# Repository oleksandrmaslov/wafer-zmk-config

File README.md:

# Wafer

Wafer is a 36 key ultra-thin split keyboard that stays between 4–8 mm thick,
depending where you measure it. It runs on an ISP1807 with an nPM1300 PMIC, and
the full aluminium case snaps together with magnets for a clean profile.
Kailh PG1316S switches, a nice!view display and a 250 mAh LiPo in each half.
It runs ZMK over Bluetooth LE or USB.

More photos and the full story are on
[the project page](https://oleksandrmaslov.github.io/portfolio/Wafer.html).

***

## LAYOUT

Default layout is shown above; layers and firmware live in this repo. `main`
keeps the standard QWERTY layout, and my daily-use keymap is on
[`personal-layout`](https://github.com/oleksandrmaslov/wafer-zmk-config/tree/personal-layout).
Copy [wafer.keymap](boards/waferboard/wafer/wafer.keymap) to `config/wafer.keymap`
to change it, and put your other settings in [config/wafer.conf](config/wafer.conf).

The default build keeps the local nice!view status screen and
[zmk-soft-off-plus](https://github.com/oleksandrmaslov/zmk-soft-off-plus).
Hold the power button for about 1.8 seconds, then release it to turn both
connected halves off. On battery, hold each half's button for 1.5 seconds to
wake it. USB wake bypass allows a short press when USB power is detected.
Triple-tap the plugged-in half's button while awake to enter its bootloader.

The [nPM1300 battery driver](modules/npm1300_vbat/) lives here. Soft-off-plus and
[zmk-split-hid-display](https://github.com/oleksandrmaslov/zmk-split-hid-display)
stay in their own separate repos. The HID display module is optional and adds
the host information shown in the newer display photos. Check **hid_display** in a manual
[build workflow](https://github.com/oleksandrmaslov/wafer-zmk-config/actions/workflows/build.yml)
run to build that version too.

[Build and flashing guide](docs/building.md) ·
[Board files](boards/waferboard/wafer/README.md) ·
[Build validation](docs/validation.md)

***

## PCB

[Here](https://github.com/oleksandrmaslov/wafer-keyboard/tree/main/pcb) you can
find the PCB and production files in the separate `wafer-keyboard` repo. There
are two versions, with mousebites for production and without them.

***

## BOM

The full Bill of Materials is in the hardware repo:

- [BOM (JLCPCB production)](https://github.com/oleksandrmaslov/wafer-keyboard/blob/main/pcb/jlcpcb/production_files/BOM-wafer_keyboard_v3_production.csv)
- [Component placement](https://github.com/oleksandrmaslov/wafer-keyboard/blob/main/pcb/jlcpcb/production_files/CPL-wafer_keyboard_v3_production.csv)
- [Original price breakdown](https://github.com/oleksandrmaslov/wafer-keyboard/blob/main/pcb/Keyboard%20Price.csv)

***

## CASE

These models are for CNC:

- [Left case STEP](https://github.com/oleksandrmaslov/wafer-keyboard/blob/main/case/wafer_case_left.step)
- [Right case STEP](https://github.com/oleksandrmaslov/wafer-keyboard/blob/main/case/wafer_case_right.step)
- [Thread drawing](https://github.com/oleksandrmaslov/wafer-keyboard/blob/main/case/Wafer%20threads%20drawing.pdf)

See the [hardware repo guide](docs/hardware-repository.md) for the file split and
personal-build permissions.

***

## PHOTOS

Art on the back:

And in KiCad:

***

## LICENSE

### Software source code and firmware configuration

Firmware code, keymaps, devicetrees, configuration and software documentation use
the [MIT License](LICENSE). This includes the physical-layout definitions ZMK
needs to use the keyboard.

### Photos, artwork and hardware designs

Photos, renders, artwork and the illustrated layout use
[CC BY-NC 4.0](assets/LICENSE). You can share and modify them for noncommercial
use with attribution. [Photo sources and credits](assets/README.md).

PCB/CAD files in `wafer-keyboard` also use CC BY-NC 4.0, with explicit permission
for personal builds, modifications and paying a fabricator for your own copies.
Commercial production needs separate written permission. The
[licensing guide](docs/hardware-repository.md) explains the scope and contact.

Copyright (c) 2025 The ZMK Contributors and (c) 2026 Oleksandr Maslov. Existing
third-party notices and earlier licence grants remain applicable.

***

## CREDITS

### INSPIRATION

Inspired by the [Totem Keyboard](https://github.com/GEIGEIGEIST/TOTEM) and [Mikehive](https://github.com/mikeholscher/zmk-config-mikefive), but with a slimmer profile and magnets for usability. Big thanks to Rasmus for introducing me to the ISP1807.

### HELP FIXING THINGS

People who helped me create this board and fix stuff:

#### PCB

- [Rasmus Koit](https://github.com/rasmuskoit)
- [Eden](https://github.com/galaxyeden)
#### CASE

- [Vlad Vodkin (consulted me to build this case, huge thanks)](https://t.me/vlad30303)

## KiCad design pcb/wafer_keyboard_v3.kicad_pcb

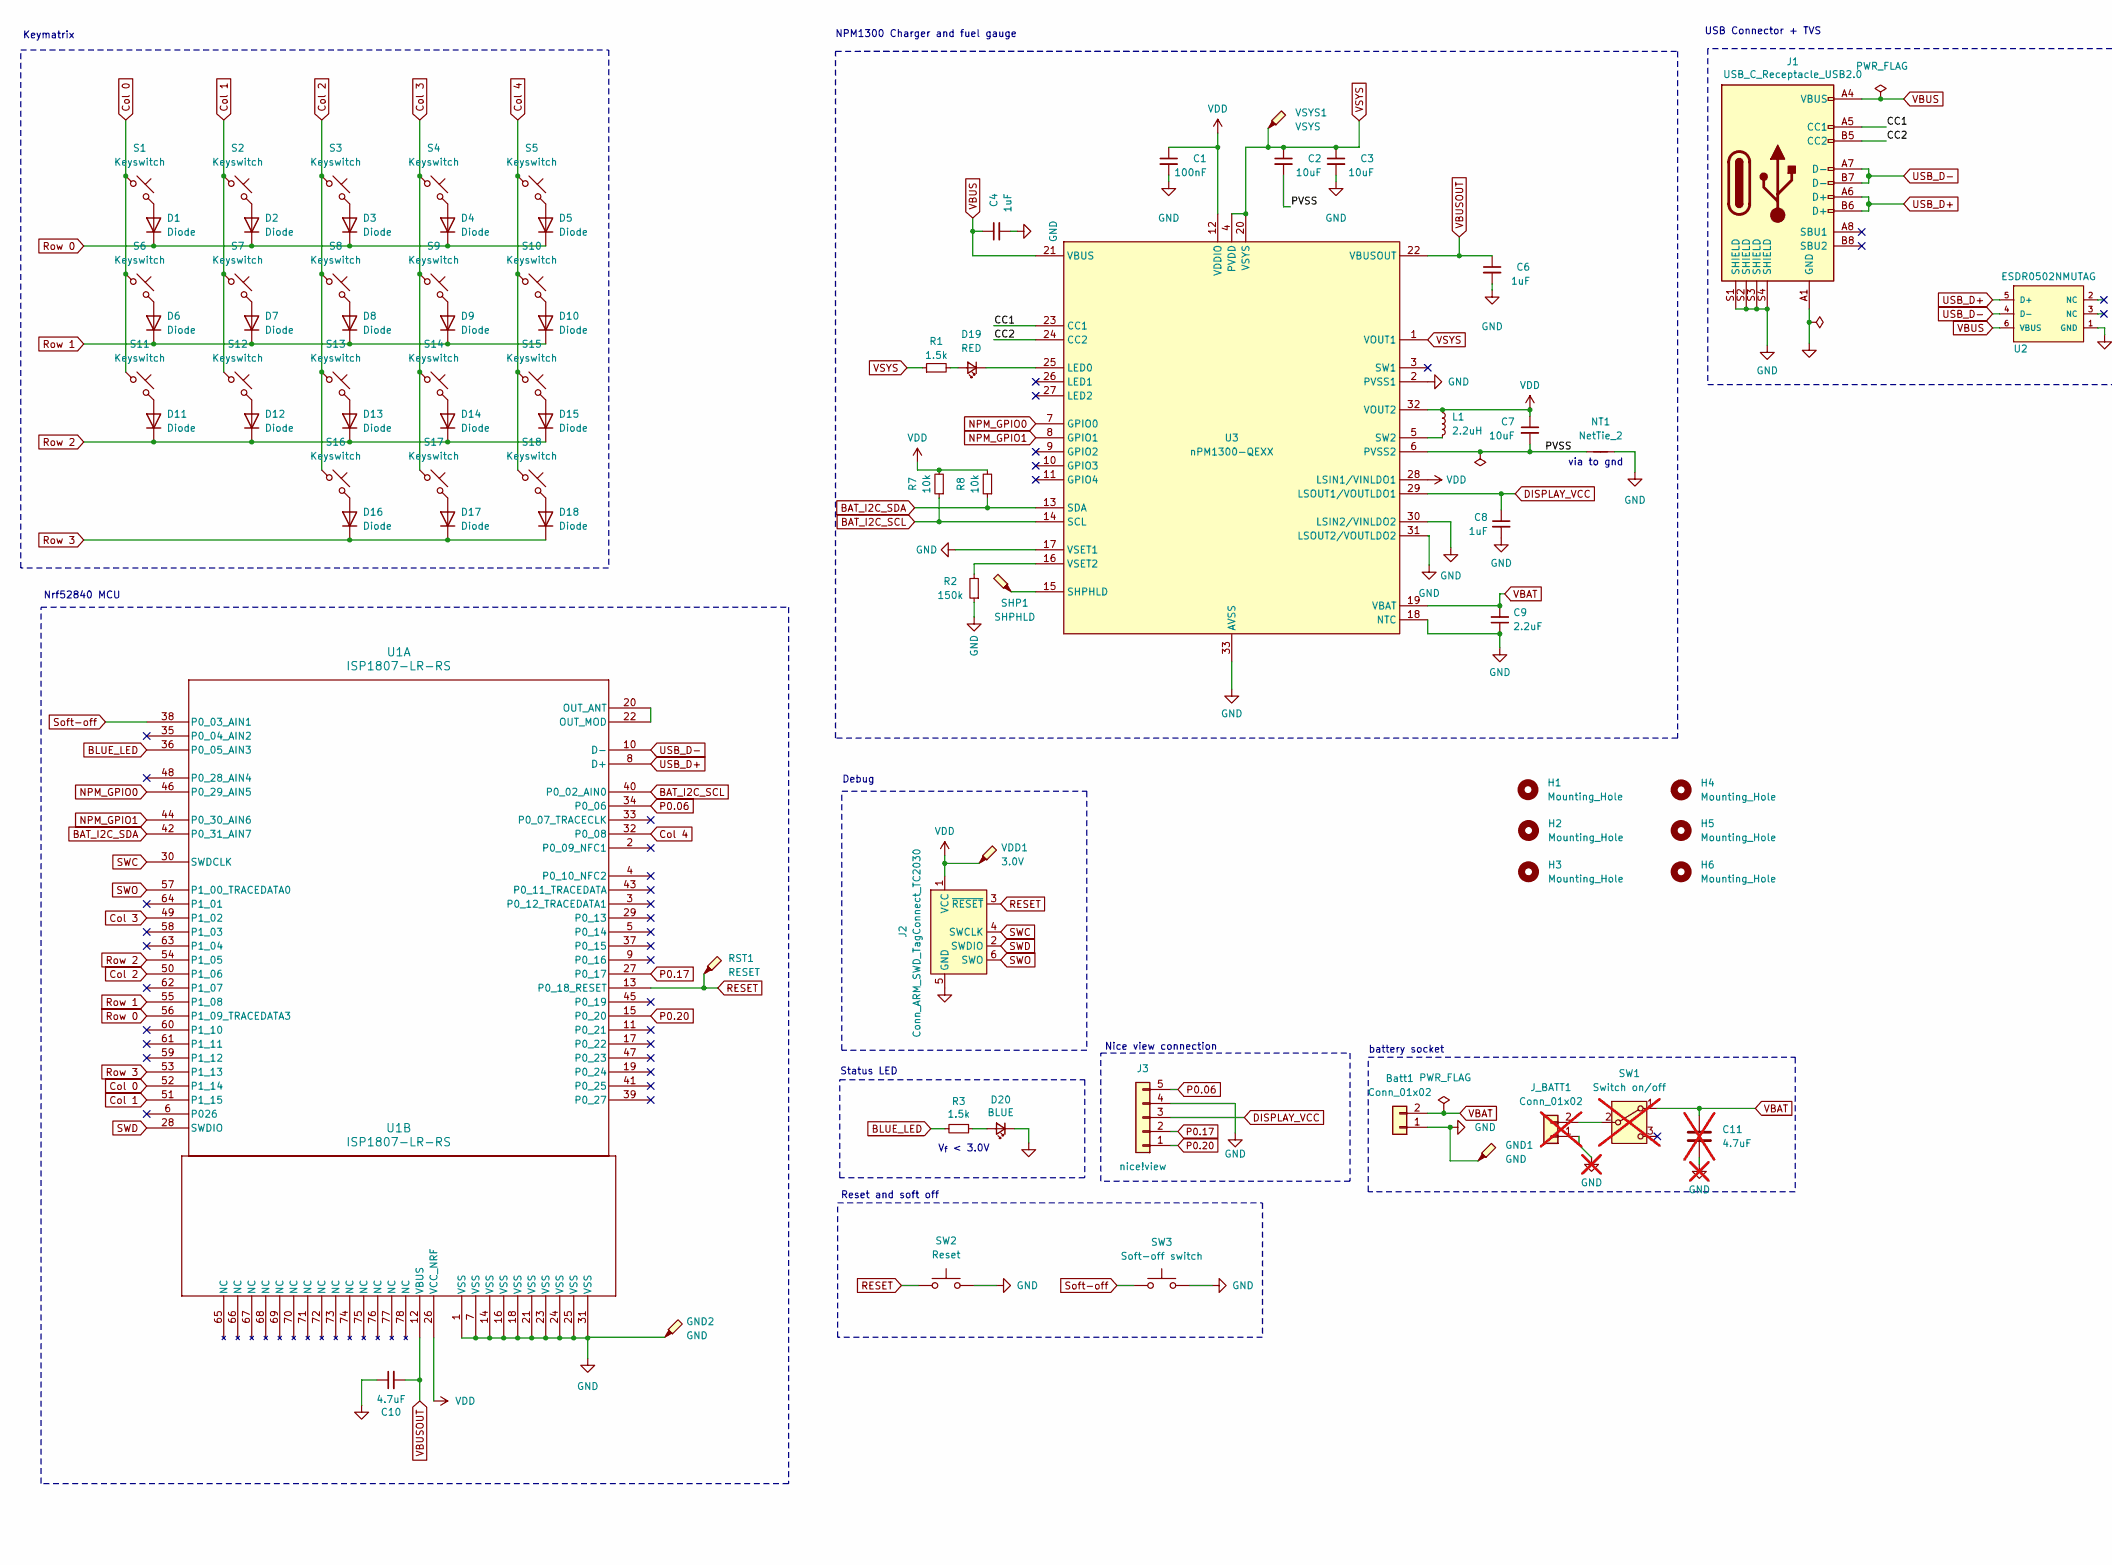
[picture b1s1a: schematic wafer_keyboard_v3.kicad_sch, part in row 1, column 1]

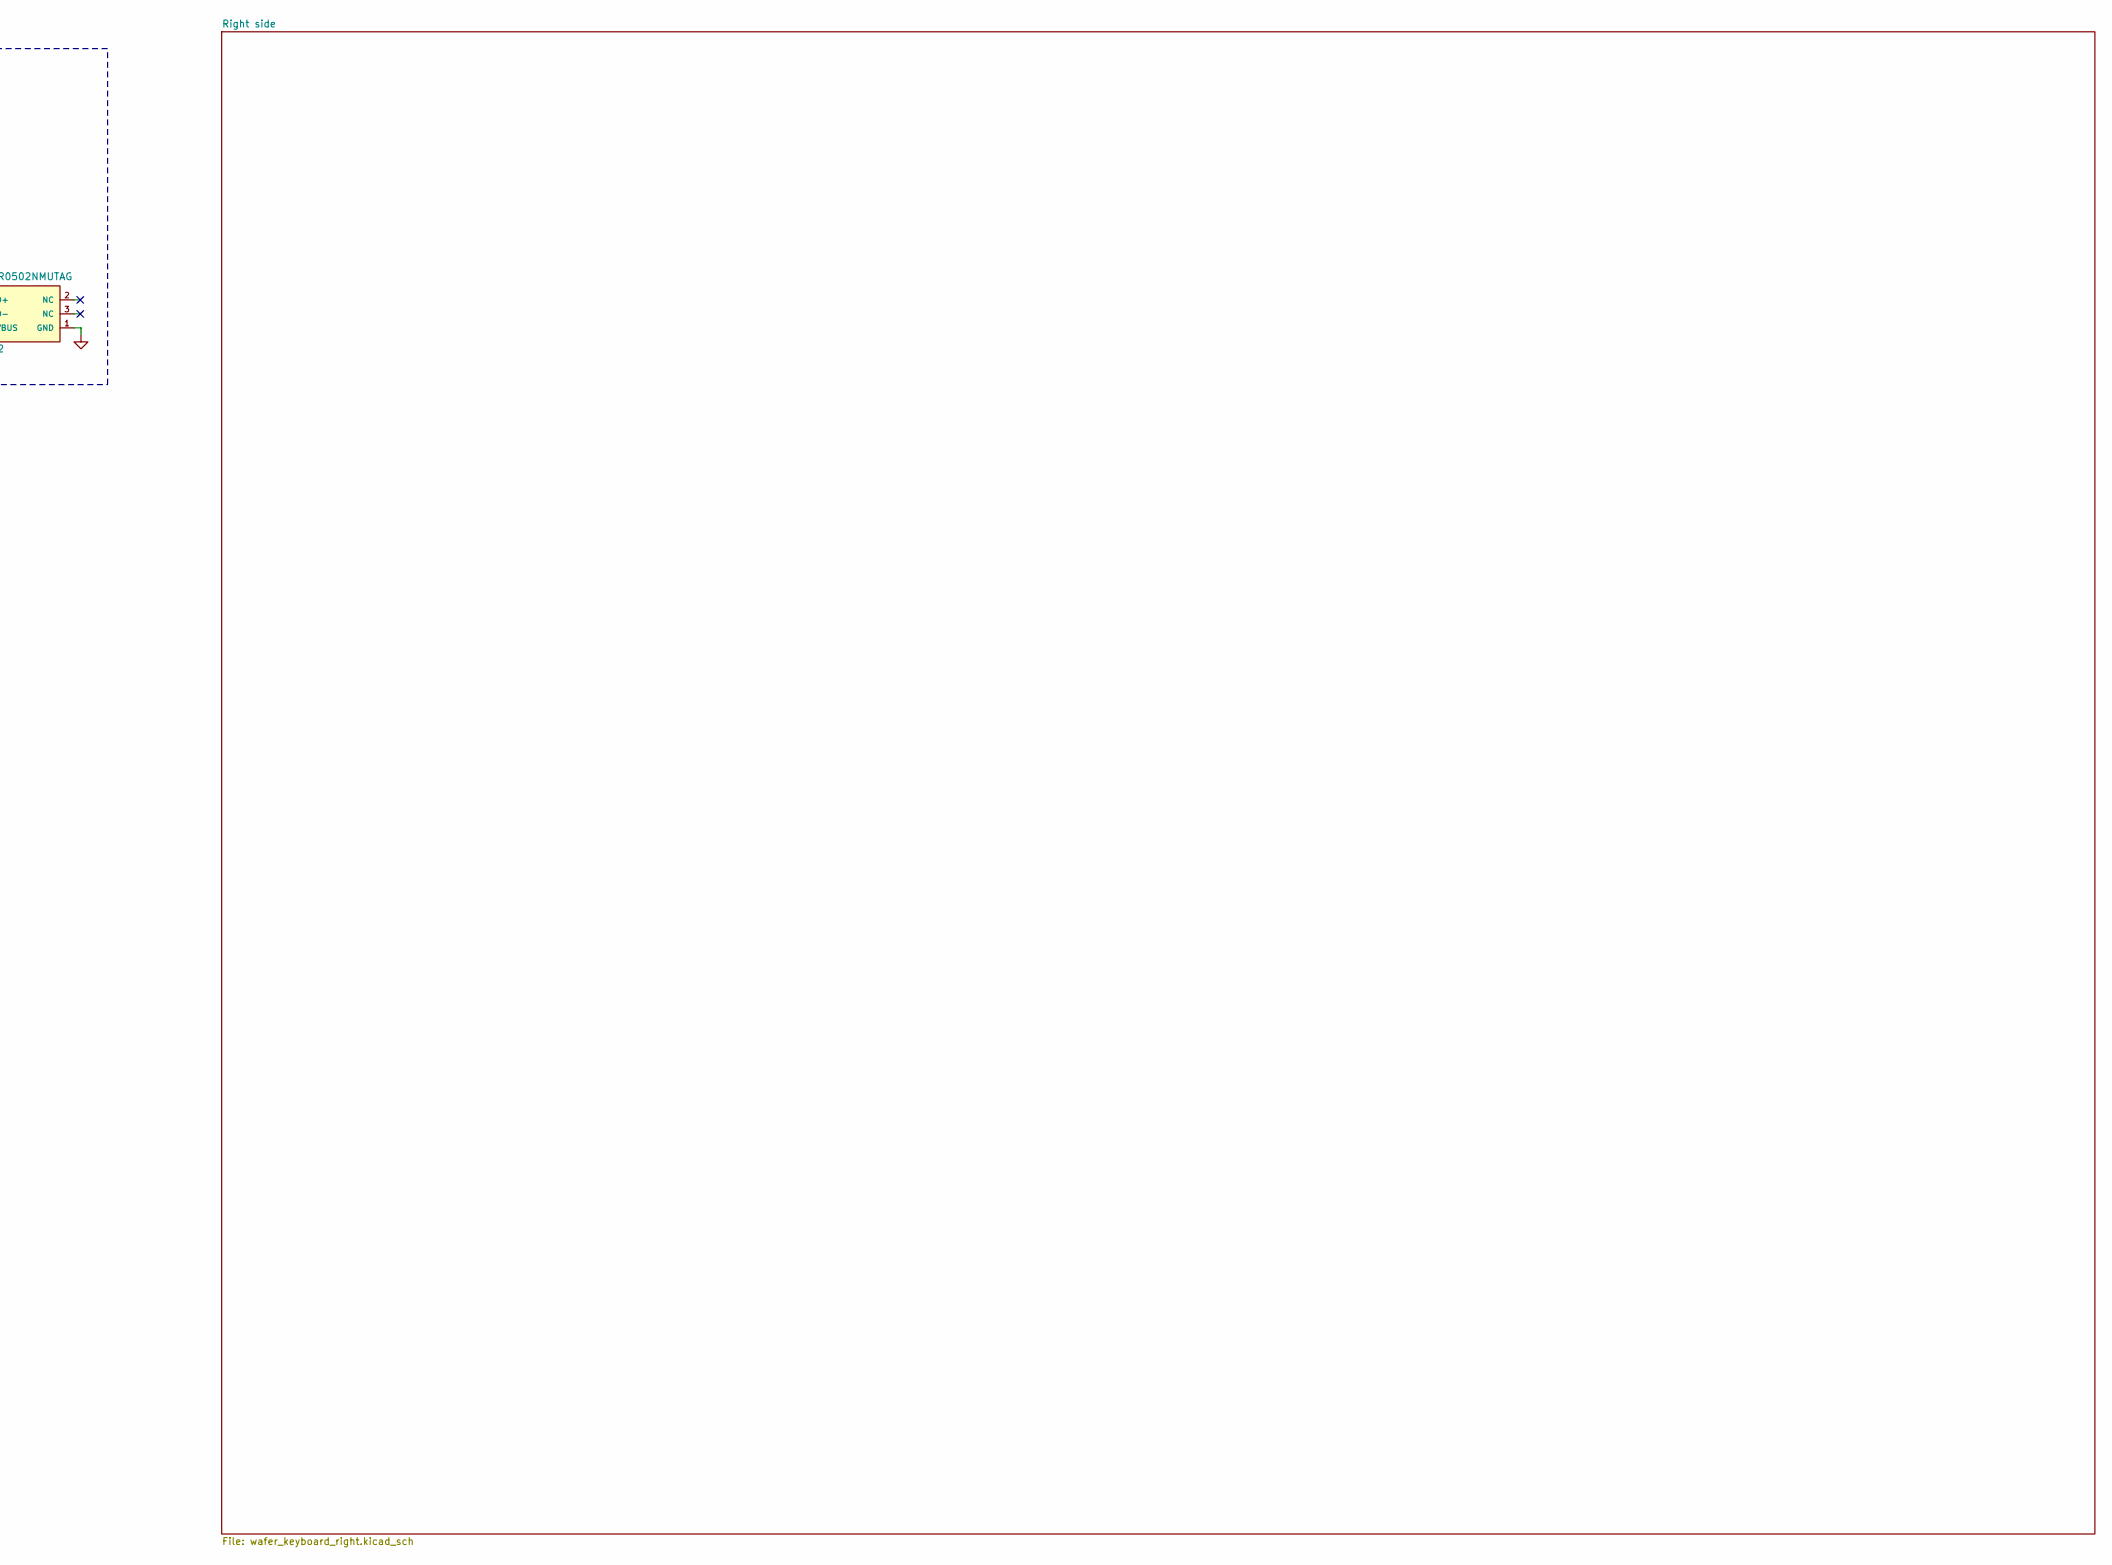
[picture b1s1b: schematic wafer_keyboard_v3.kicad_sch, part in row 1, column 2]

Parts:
Batt1: Conn_01x02; JST_SHL_SM02B-SHLS-TF_1x02-1MP_P1.00mm_Horizontal
C1: 100nF; C_0201_0603Metric; Manufacturer Part CL05A105KO5NNNC; LCSC Part C52923
C2, C3: 10uF; C_0603_1608Metric; Manufacturer Part CL05A105KO5NNNC; LCSC Part C52923
C4, C6: 1uF; C_0402_1005Metric; Manufacturer Part CL05A105KO5NNNC; LCSC Part C52923
C7: 10uF; C_0603_1608Metric; Mouser Part Number 603-CC603KRX7R5BB105
C8: 1uF; C_0402_1005Metric; Mouser Part Number 603-CC603KRX7R5BB105
C9: 2.2uF; C_0402_1005Metric; Mouser Part Number 603-CC603KRX7R5BB105
C10: 4.7uF; C_0402_1005Metric; Manufacturer Part CL05A475KP5NRNC; LCSC Part C368809
C11: 4.7uF; Capacitor_0402_1005M-nosilk; not fitted
D1, D2, D3, D4, D5, D6, D7, D8, D9, D10, D11, D12, D13, D14, D15, D16, D17, D18: Diode; Diode_SOD-123
D19: RED; LED_0402_1005Metric; Manufacturer Part LTST-C281KFKT-5A; LCSC Part C364554
D20: BLUE; LED_0402_1005Metric; Manufacturer Part LTST-C281TBKT-5A; LCSC Part C364550
GND1, GND2: GND; TestPoint_Pad_D1.0mm
H1, H2, H3, H4, H5, H6: Mounting_Hole; MountingHole_4.3mm_M4
J1: USB_C_Receptacle_USB2.0; USB-C_C168688; LCSC Part C168688
J2: Conn_ARM_SWD_TagConnect_TC2030; Tag-Connect_TC2030-IDC-FP_2x03_P1.27mm_Vertical
J3: nice!view; display_nice_view
J_BATT1: Conn_01x02; Battery; not fitted
L1: 2.2uH; L_0805_2012Metric; Manufacturer_Part_Number MLZ2012A2R2WT000; Mouser Part Number 810-MLZ2012A2R2WT000
NT1: NetTie_2; NetTie-2_SMD_Pad0.5mm
R1: 1.5k; R_0402_1005Metric; Manufacturer Part RC0402FR-0710KL; LCSC Part C25744
R2: 150k; R_0201_0603Metric; Manufacturer Part RC0402FR-0710KL; LCSC Part C25744
R3: 1.5k; R_0402_1005Metric; Manufacturer Part RC0402FR-071K5L; LCSC Part C114759
R7, R8: 10k; R_0201_0603Metric; Manufacturer Part RC0402FR-0710KL; LCSC Part C25744
RST1: RESET; TestPoint_Pad_D1.0mm
S1, S2, S3, S4, S5, S6, S7, S8, S9, S10, S11, S12, S13, S14, S15, S16, S17, S18: Keyswitch; CPG1316S01D02_front_mikefives
SHP1: SHPHLD; TestPoint_Pad_D1.0mm
SW1: Switch on/off; Switch_MSK12C02; not fitted
SW2: Reset; SW-SMD_L3.0-W2.0-LS3.5
SW3: Soft-off switch; Panasonic_EVQPUL_EVQPUC
U1: ISP1807-LR-RS
U2: ESDR0502NMUTAG; UDFN-6_1.2x1.0mm_P0.4mm; Manufacturer Part ESDR0502NMUTBG; LCSC Part C94372
U3: nPM1300-QEXX; QFN-32-1EP_5x5mm_P0.5mm_EP3.6x3.6mm_ThermalVias
VDD1: 3.0V; TestPoint_Pad_D1.0mm
VSYS1: VSYS; TestPoint_Pad_D1.0mm

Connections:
/CC1: J1.A5 (CC1), U3.23 (CC1)
/CC2: J1.B5 (CC2), U3.24 (CC2)
/PVSS: C2.2, C7.2, NT1.1, U3.6 (PVSS2)
BAT_I2C_SCL: R7.1, U1.40 (P0_02_AIN0), U3.14 (SCL)
BAT_I2C_SDA: R8.1, U1.42 (P0_31_AIN7), U3.13 (SDA)
BLUE_LED: R3.2, U1.36 (P0_05_AIN3)
Col 0: S1.1, S6.1, S11.1, U1.52 (P1_14)
Col 1: S2.1, S7.1, S12.1, U1.51 (P1_15)
Col 2: S3.1, S8.1, S13.1, S16.1, U1.50 (P1_06)
Col 3: S4.1, S9.1, S14.1, S17.1, U1.49 (P1_02)
Col 4: S5.1, S10.1, S15.1, S18.1, U1.32 (P0_08)
DISPLAY_VCC: C8.1, J3.3, U3.29 (LSOUT1/VOUTLDO1)
GND: Batt1.1, C1.2, C3.2, C4.2, C6.2, C8.2, C9.1, C10.1, C11.2, D20.1 (K), GND1.1, GND2.1, J1.A1 (GND), J1.S1 (SHIELD), J1.S2 (SHIELD), J1.S3 (SHIELD), J1.S4 (SHIELD), J2.5 (GND), J3.4, J_BATT1.1, NT1.2, R2.1, SW2.2, SW3.2, U1.1 (VSS), U1.7 (VSS), U1.14 (VSS), U1.16 (VSS), U1.18 (VSS), U1.21 (VSS), U1.23 (VSS), U1.24 (VSS), U1.25 (VSS), U1.31 (VSS), U2.1 (GND), U3.2 (PVSS1), U3.17 (VSET1), U3.18 (NTC), U3.30 (LSIN2/VINLDO2), U3.31 (LSOUT2/VOUTLDO2), U3.33 (AVSS)
NPM_GPIO0: U1.46 (P0_29_AIN5), U3.7 (GPIO0)
NPM_GPIO1: U1.44 (P0_30_AIN6), U3.8 (GPIO1)
unnamed: D1.2 (A), S1.2
unnamed: D2.2 (A), S2.2
unnamed: D3.2 (A), S3.2
unnamed: D4.2 (A), S4.2
unnamed: D5.2 (A), S5.2
unnamed: D6.2 (A), S6.2
unnamed: D7.2 (A), S7.2
unnamed: D8.2 (A), S8.2
unnamed: D9.2 (A), S9.2
unnamed: D10.2 (A), S10.2
unnamed: D11.2 (A), S11.2
unnamed: D12.2 (A), S12.2
unnamed: D13.2 (A), S13.2
unnamed: D14.2 (A), S14.2
unnamed: D15.2 (A), S15.2
unnamed: D16.2 (A), S16.2
unnamed: D17.2 (A), S17.2
unnamed: D18.2 (A), S18.2
unnamed: D19.2 (A), R1.2
unnamed: D19.1 (K), U3.25 (LED0)
unnamed: D20.2 (A), R3.1
unnamed: J_BATT1.2, SW1.2 (B)
unnamed: U1.20 (OUT_ANT), U1.22 (OUT_MOD)
unnamed: SHP1.1, U3.15 (SHPHLD)
unnamed: L1.2, U3.5 (SW2)
unnamed: R2.2, U3.16 (VSET2)
P0.06: J3.5, U1.34 (P0_06)
P0.17: J3.2, U1.27 (P0_17)
P0.20: J3.1, U1.15 (P0_20)
RESET: J2.3 (~RESET), RST1.1, SW2.1, U1.13 (P0_18_RESET)
Row 0: D1.1 (K), D2.1 (K), D3.1 (K), D4.1 (K), D5.1 (K), U1.56 (P1_09_TRACEDATA3)
Row 1: D6.1 (K), D7.1 (K), D8.1 (K), D9.1 (K), D10.1 (K), U1.55 (P1_08)
Row 2: D11.1 (K), D12.1 (K), D13.1 (K), D14.1 (K), D15.1 (K), U1.54 (P1_05)
Row 3: D16.1 (K), D17.1 (K), D18.1 (K), U1.53 (P1_13)
SWC: J2.4 (SWCLK), U1.30 (SWDCLK)
SWD: J2.2 (SWDIO), U1.28 (SWDIO)
SWO: J2.6 (SWO), U1.57 (P1_00_TRACEDATA0)
Soft-off: SW3.1, U1.38 (P0_03_AIN1)
USB_D+: J1.A6 (D+), J1.B6 (D+), U1.8 (D+), U2.5 (D+)
USB_D-: J1.A7 (D-), J1.B7 (D-), U1.10 (D-), U2.4 (D-)
VBAT: Batt1.2, C9.2, C11.1, SW1.1 (A), U3.19 (VBAT)
VBUS: C4.1, J1.A4 (VBUS), U2.6 (VBUS), U3.21 (VBUS)
VBUSOUT: C6.1, C10.2, U1.12 (VBUS), U3.22 (VBUSOUT)
VDD: C1.1, C7.1, J2.1 (VCC), L1.1, R7.2, R8.2, U1.26 (VCC_NRF), U3.12 (VDDIO), U3.28 (LSIN1/VINLDO1), U3.32 (VOUT2), VDD1.1
VSYS: C2.1, C3.1, R1.1, U3.1 (VOUT1), U3.4 (PVDD), U3.20 (VSYS), VSYS1.1

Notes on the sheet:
NPM1300 Charger and fuel gauge
Nice view connection
V_{f} < 3.0V
battery socket
Debug
Keymatrix
via to gnd
USB Connector + TVS
Status LED
Nrf52840 MCU
Reset and soft off

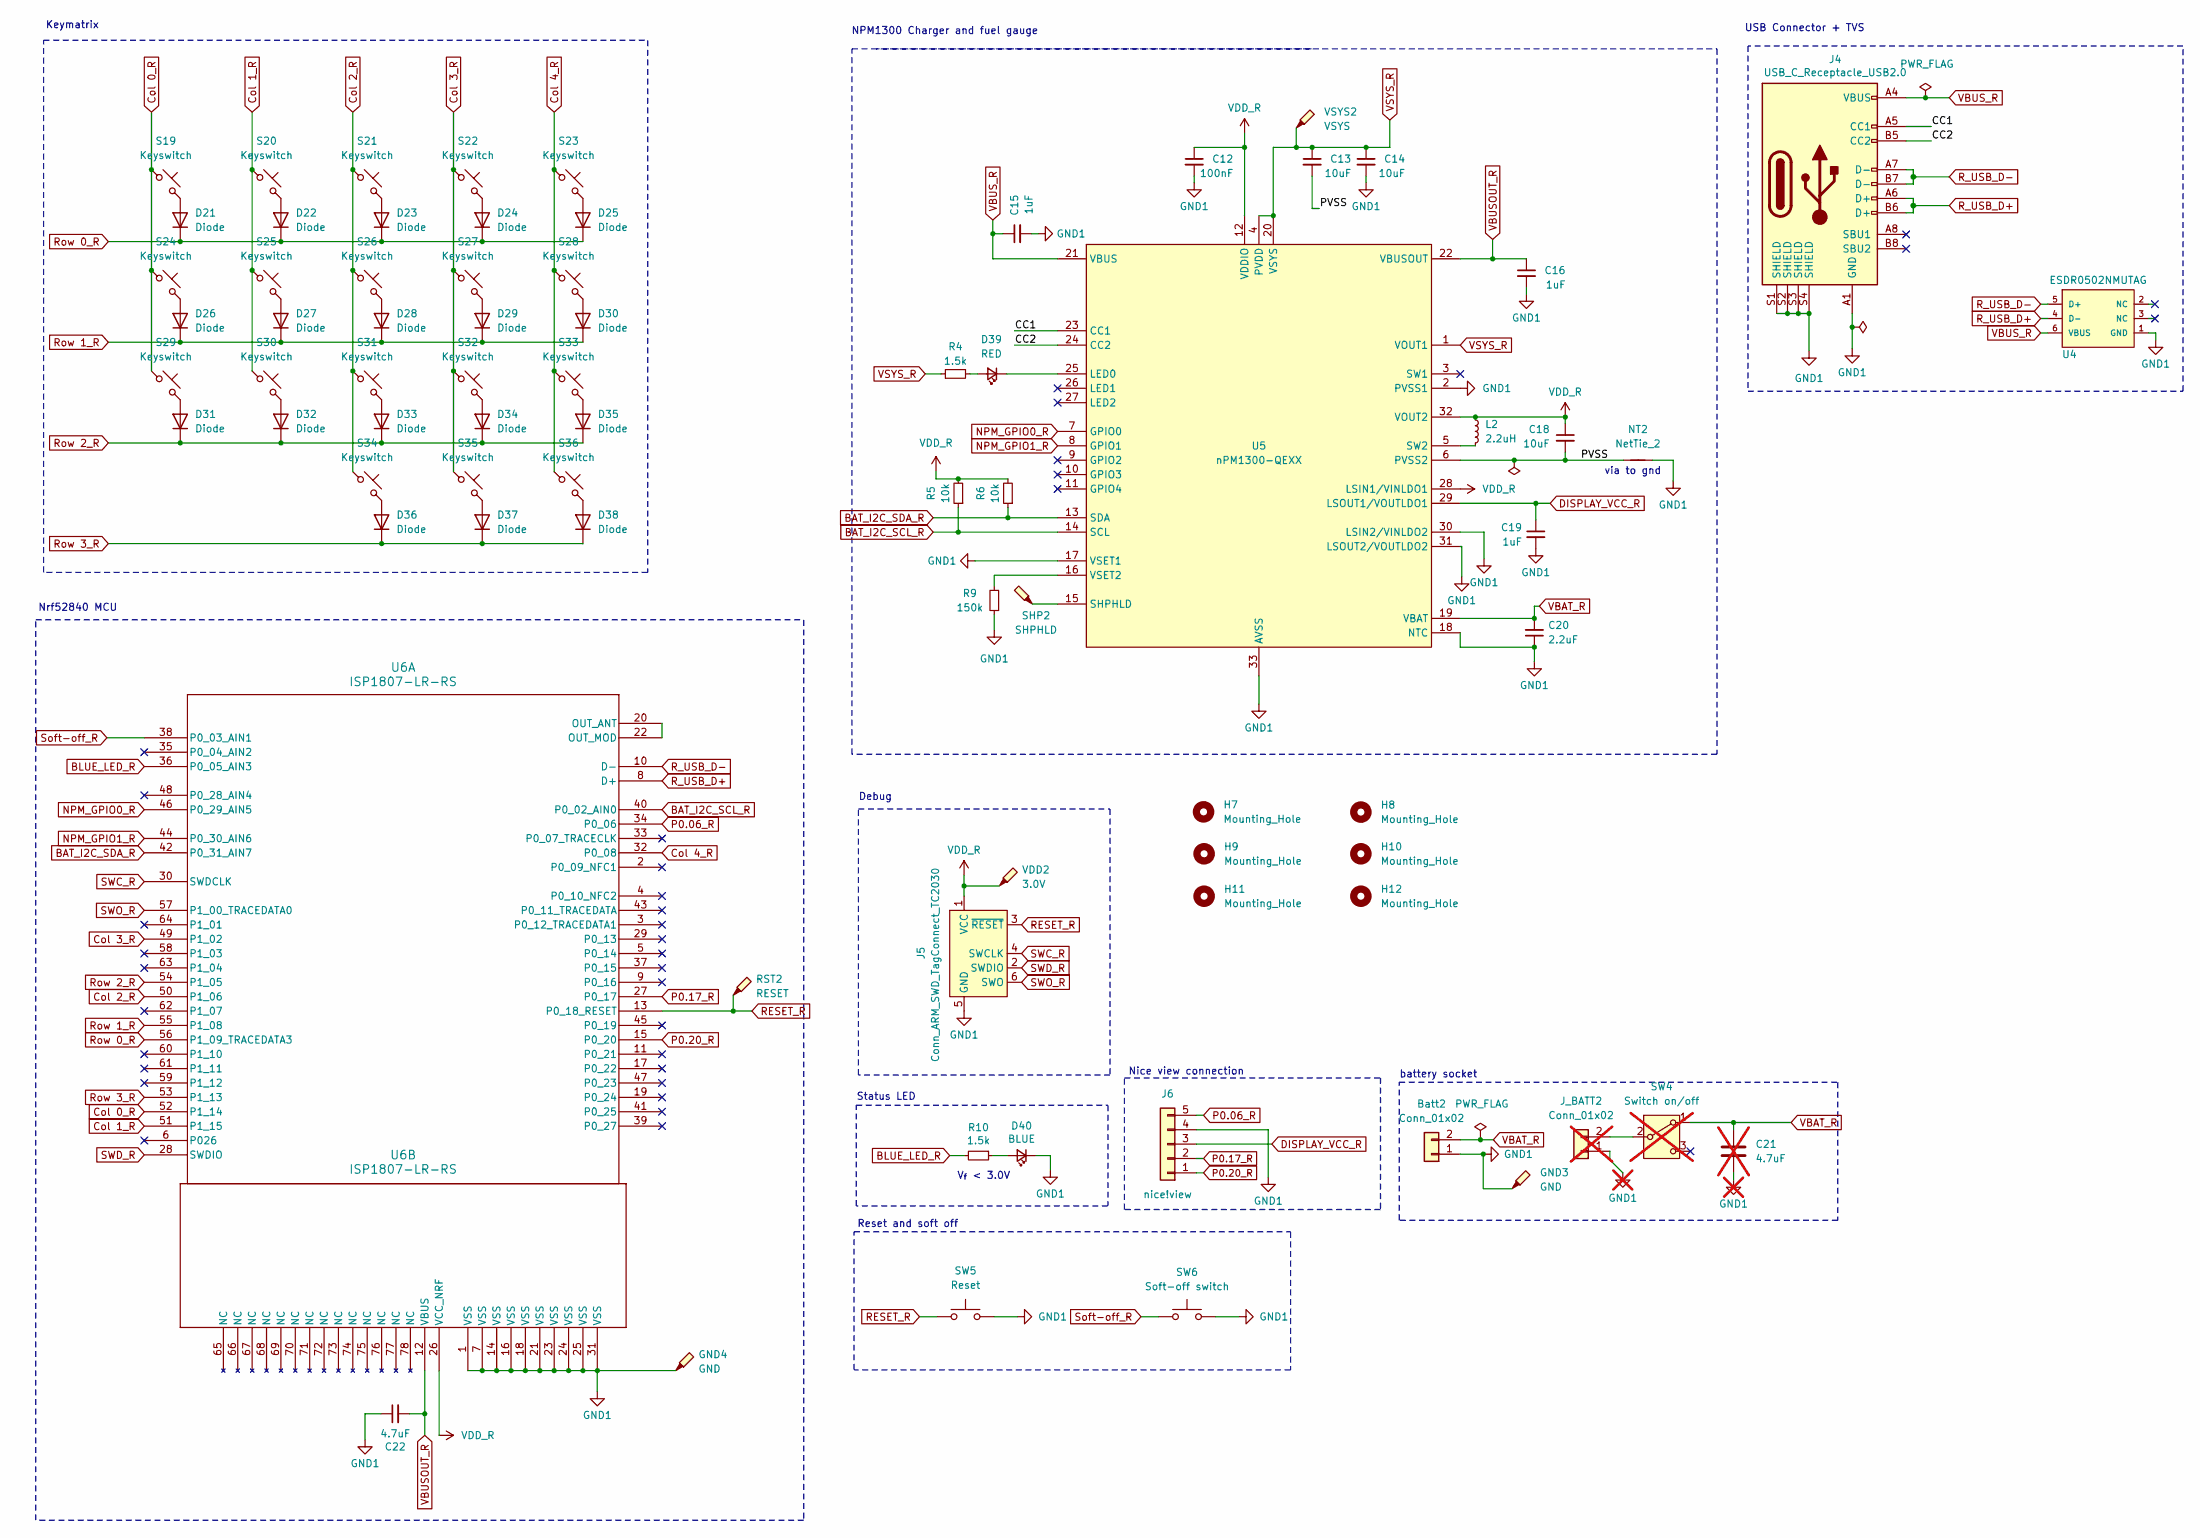
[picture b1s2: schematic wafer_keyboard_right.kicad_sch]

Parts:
Batt2: Conn_01x02; JST_SHL_SM02B-SHLS-TF_1x02-1MP_P1.00mm_Horizontal
C12: 100nF; C_0201_0603Metric; Manufacturer Part CL05A105KO5NNNC; LCSC Part C52923
C13, C14: 10uF; C_0603_1608Metric; Manufacturer Part CL05A105KO5NNNC; LCSC Part C52923
C15, C16: 1uF; C_0402_1005Metric; Manufacturer Part CL05A105KO5NNNC; LCSC Part C52923
C18: 10uF; C_0603_1608Metric; Mouser Part Number 603-CC603KRX7R5BB105
C19: 1uF; C_0402_1005Metric; Mouser Part Number 603-CC603KRX7R5BB105
C20: 2.2uF; C_0402_1005Metric; Mouser Part Number 603-CC603KRX7R5BB105
C21: 4.7uF; Capacitor_0402_1005M-nosilk; not fitted
C22: 4.7uF; C_0402_1005Metric; Manufacturer Part CL05A475KP5NRNC; LCSC Part C368809
D21, D22, D23, D24, D25, D26, D27, D28, D29, D30, D31, D32, D33, D34, D35, D36, D37, D38: Diode; Diode_SOD-123
D39: RED; LED_0402_1005Metric; Manufacturer Part LTST-C281KFKT-5A; LCSC Part C364554
D40: BLUE; LED_0402_1005Metric; Manufacturer Part LTST-C281TBKT-5A; LCSC Part C364550
GND3, GND4: GND; TestPoint_Pad_D1.0mm
H7, H8, H9, H10, H11, H12: Mounting_Hole; MountingHole_4.3mm_M4
J4: USB_C_Receptacle_USB2.0; USB-C_C168688; LCSC Part C168688
J5: Conn_ARM_SWD_TagConnect_TC2030; Tag-Connect_TC2030-IDC-FP_2x03_P1.27mm_Vertical
J6: nice!view; display_nice_view
J_BATT2: Conn_01x02; Battery; not fitted
L2: 2.2uH; L_0805_2012Metric; Manufacturer_Part_Number MLZ2012A2R2WT000; Mouser Part Number 810-MLZ2012A2R2WT000
NT2: NetTie_2; NetTie-2_SMD_Pad0.5mm
R4: 1.5k; R_0402_1005Metric; Manufacturer Part RC0402FR-0710KL; LCSC Part C25744
R5, R6: 10k; R_0201_0603Metric; Manufacturer Part RC0402FR-0710KL; LCSC Part C25744
R9: 150k; R_0201_0603Metric; Manufacturer Part RC0402FR-0710KL; LCSC Part C25744
R10: 1.5k; R_0402_1005Metric; Manufacturer Part RC0402FR-071K5L; LCSC Part C114759
RST2: RESET; TestPoint_Pad_D1.0mm
S19, S20, S21, S22, S23, S24, S25, S26, S27, S28, S29, S30, S31, S32, S33, S34, S35, S36: Keyswitch; CPG1316S01D02_front_mikefives
SHP2: SHPHLD; TestPoint_Pad_D1.0mm
SW4: Switch on/off; Switch_MSK12C02; not fitted
SW5: Reset; SW-SMD_L3.0-W2.0-LS3.5
SW6: Soft-off switch; Panasonic_EVQPUL_EVQPUC
U4: ESDR0502NMUTAG; UDFN-6_1.2x1.0mm_P0.4mm; Manufacturer Part ESDR0502NMUTBG; LCSC Part C94372
U5: nPM1300-QEXX; QFN-32-1EP_5x5mm_P0.5mm_EP3.6x3.6mm_ThermalVias
U6: ISP1807-LR-RS
VDD2: 3.0V; TestPoint_Pad_D1.0mm
VSYS2: VSYS; TestPoint_Pad_D1.0mm

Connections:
/Right side/CC1: J4.A5 (CC1), U5.23 (CC1)
/Right side/CC2: J4.B5 (CC2), U5.24 (CC2)
/Right side/PVSS: C13.2, C18.2, NT2.1, U5.6 (PVSS2)
BAT_I2C_SCL_R: R5.1, U5.14 (SCL), U6.40 (P0_02_AIN0)
BAT_I2C_SDA_R: R6.1, U5.13 (SDA), U6.42 (P0_31_AIN7)
BLUE_LED_R: R10.2, U6.36 (P0_05_AIN3)
Col 0_R: S19.1, S24.1, S29.1, U6.52 (P1_14)
Col 1_R: S20.1, S25.1, S30.1, U6.51 (P1_15)
Col 2_R: S21.1, S26.1, S31.1, S34.1, U6.50 (P1_06)
Col 3_R: S22.1, S27.1, S32.1, S35.1, U6.49 (P1_02)
Col 4_R: S23.1, S28.1, S33.1, S36.1, U6.32 (P0_08)
DISPLAY_VCC_R: C19.1, J6.3, U5.29 (LSOUT1/VOUTLDO1)
GND1: Batt2.1, C12.2, C14.2, C15.2, C16.2, C19.2, C20.1, C21.2, C22.1, D40.1 (K), GND3.1, GND4.1, J4.A1 (GND), J4.S1 (SHIELD), J4.S2 (SHIELD), J4.S3 (SHIELD), J4.S4 (SHIELD), J5.5 (GND), J6.4, J_BATT2.1, NT2.2, R9.1, SW5.2, SW6.2, U4.1 (GND), U5.2 (PVSS1), U5.17 (VSET1), U5.18 (NTC), U5.30 (LSIN2/VINLDO2), U5.31 (LSOUT2/VOUTLDO2), U5.33 (AVSS), U6.1 (VSS), U6.7 (VSS), U6.14 (VSS), U6.16 (VSS), U6.18 (VSS), U6.21 (VSS), U6.23 (VSS), U6.24 (VSS), U6.25 (VSS), U6.31 (VSS)
NPM_GPIO0_R: U5.7 (GPIO0), U6.46 (P0_29_AIN5)
NPM_GPIO1_R: U5.8 (GPIO1), U6.44 (P0_30_AIN6)
unnamed: D21.2 (A), S19.2
unnamed: D22.2 (A), S20.2
unnamed: D23.2 (A), S21.2
unnamed: D24.2 (A), S22.2
unnamed: D25.2 (A), S23.2
unnamed: D26.2 (A), S24.2
unnamed: D27.2 (A), S25.2
unnamed: D28.2 (A), S26.2
unnamed: D29.2 (A), S27.2
unnamed: D30.2 (A), S28.2
unnamed: D31.2 (A), S29.2
unnamed: D32.2 (A), S30.2
unnamed: D33.2 (A), S31.2
unnamed: D34.2 (A), S32.2
unnamed: D35.2 (A), S33.2
unnamed: D36.2 (A), S34.2
unnamed: D37.2 (A), S35.2
unnamed: D38.2 (A), S36.2
unnamed: D39.2 (A), R4.2
unnamed: D39.1 (K), U5.25 (LED0)
unnamed: D40.2 (A), R10.1
unnamed: J_BATT2.2, SW4.2 (B)
unnamed: SHP2.1, U5.15 (SHPHLD)
unnamed: L2.2, U5.5 (SW2)
unnamed: R9.2, U5.16 (VSET2)
unnamed: U6.20 (OUT_ANT), U6.22 (OUT_MOD)
P0.06_R: J6.5, U6.34 (P0_06)
P0.17_R: J6.2, U6.27 (P0_17)
P0.20_R: J6.1, U6.15 (P0_20)
RESET_R: J5.3 (~RESET), RST2.1, SW5.1, U6.13 (P0_18_RESET)
R_USB_D+: J4.A6 (D+), J4.B6 (D+), U4.4 (D-), U6.8 (D+)
R_USB_D-: J4.A7 (D-), J4.B7 (D-), U4.5 (D+), U6.10 (D-)
Row 0_R: D21.1 (K), D22.1 (K), D23.1 (K), D24.1 (K), D25.1 (K), U6.56 (P1_09_TRACEDATA3)
Row 1_R: D26.1 (K), D27.1 (K), D28.1 (K), D29.1 (K), D30.1 (K), U6.55 (P1_08)
Row 2_R: D31.1 (K), D32.1 (K), D33.1 (K), D34.1 (K), D35.1 (K), U6.54 (P1_05)
Row 3_R: D36.1 (K), D37.1 (K), D38.1 (K), U6.53 (P1_13)
SWC_R: J5.4 (SWCLK), U6.30 (SWDCLK)
SWD_R: J5.2 (SWDIO), U6.28 (SWDIO)
SWO_R: J5.6 (SWO), U6.57 (P1_00_TRACEDATA0)
Soft-off_R: SW6.1, U6.38 (P0_03_AIN1)
VBAT_R: Batt2.2, C20.2, C21.1, SW4.1 (A), U5.19 (VBAT)
VBUSOUT_R: C16.1, C22.2, U5.22 (VBUSOUT), U6.12 (VBUS)
VBUS_R: C15.1, J4.A4 (VBUS), U4.6 (VBUS), U5.21 (VBUS)
VDD_R: C12.1, C18.1, J5.1 (VCC), L2.1, R5.2, R6.2, U5.12 (VDDIO), U5.28 (LSIN1/VINLDO1), U5.32 (VOUT2), U6.26 (VCC_NRF), VDD2.1
VSYS_R: C13.1, C14.1, R4.1, U5.1 (VOUT1), U5.4 (PVDD), U5.20 (VSYS), VSYS2.1

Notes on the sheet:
V_{f} < 3.0V
battery socket
Status LED
Nrf52840 MCU
Keymatrix
NPM1300 Charger and fuel gauge
via to gnd
Debug
USB Connector + TVS
Reset and soft off
Nice view connection

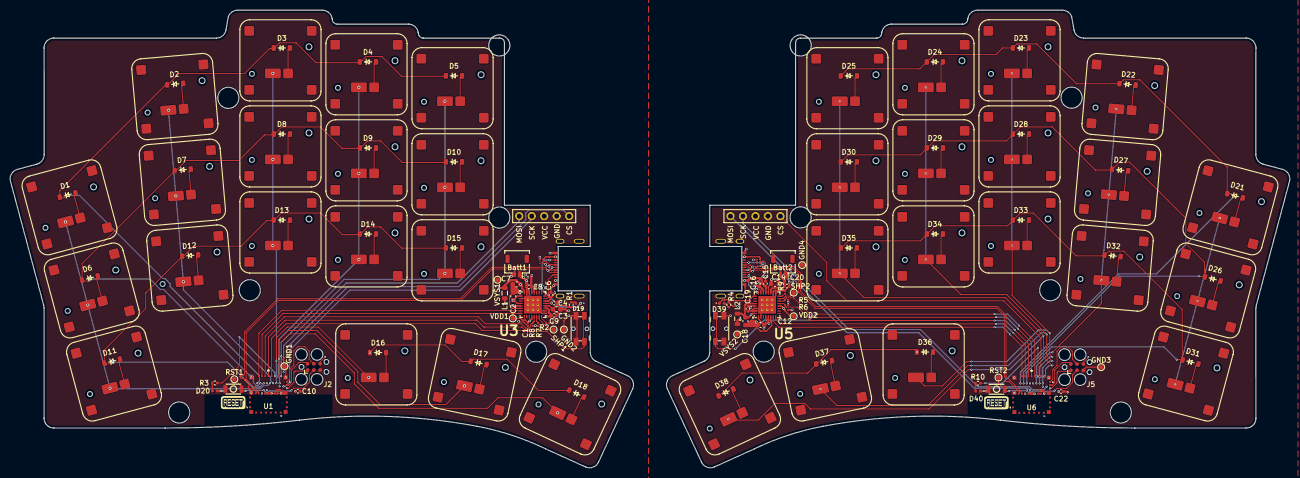
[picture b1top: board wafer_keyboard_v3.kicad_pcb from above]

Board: 6 copper layers, 260.2 x 93.0 mm, 150 parts (0 on the bottom side), 118 nets.

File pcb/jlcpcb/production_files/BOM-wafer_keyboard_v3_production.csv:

Comment,Designator,Footprint,LCSC,Quantity
1.5k,"R10,R3",R_0402_1005Metric,C114759,2
1.5k,"R1,R4",R_0402_1005Metric,C25744,2
100nF,"C1,C12",C_0201_0603Metric,C52923,2
10k,"R5,R6,R7,R8",R_0201_0603Metric,C25744,4
10uF,"C13,C14,C2,C3",C_0603_1608Metric,C52923,4
150k,"R2,R9",R_0201_0603Metric,C25744,2
1uF,"C15,C16,C4,C6",C_0402_1005Metric,C52923,4
4.7uF,"C10,C22",C_0402_1005Metric,C368809,2
BLUE,"D20,D40",LED_0402_1005Metric,C364550,2
ESDR0502NMUTAG,"U2,U4",UDFN-6_1.2x1.0mm_P0.4mm,C94372,2
RED,"D19,D39",LED_0402_1005Metric,C364554,2
USB_C_Receptacle_USB2.0,"J1,J4",USB-C_C168688,C168688,2
Keyswitch,S32,CPG1316S01D02_front_mikefives,,1
2.2uH,L2,L_0805_2012Metric,,1
Diode,D22,Diode_SOD-123,,1
Keyswitch,S26,CPG1316S01D02_front_mikefives,,1
Diode,D25,Diode_SOD-123,,1
Keyswitch,S4,CPG1316S01D02_front_mikefives,,1
Diode,D37,Diode_SOD-123,,1
nPM1300-QEXX,U3,QFN-32-1EP_5x5mm_P0.5mm_EP3.6x3.6mm_ThermalVias,,1
Diode,D31,Diode_SOD-123,,1
Keyswitch,S30,CPG1316S01D02_front_mikefives,,1
Diode,D38,Diode_SOD-123,,1
Keyswitch,S21,CPG1316S01D02_front_mikefives,,1
2.2uF,C9,C_0402_1005Metric,,1
10uF,C18,C_0603_1608Metric,,1
Keyswitch,S23,CPG1316S01D02_front_mikefives,,1
Diode,D2,Diode_SOD-123,,1
Keyswitch,S18,CPG1316S01D02_front_mikefives,,1
Diode,D35,Diode_SOD-123,,1
Keyswitch,S31,CPG1316S01D02_front_mikefives,,1
Keyswitch,S16,CPG1316S01D02_front_mikefives,,1
Diode,D24,Diode_SOD-123,,1
nPM1300-QEXX,U5,QFN-32-1EP_5x5mm_P0.5mm_EP3.6x3.6mm_ThermalVias,,1
Diode,D7,Diode_SOD-123,,1
Diode,D16,Diode_SOD-123,,1
Diode,D15,Diode_SOD-123,,1
Keyswitch,S27,CPG1316S01D02_front_mikefives,,1
Keyswitch,S1,CPG1316S01D02_front_mikefives,,1
Diode,D21,Diode_SOD-123,,1
Keyswitch,S36,CPG1316S01D02_front_mikefives,,1
Reset,SW2,SW-SMD_L3.0-W2.0-LS3.5,,1
Keyswitch,S11,CPG1316S01D02_front_mikefives,,1
Diode,D3,Diode_SOD-123,,1
Diode,D33,Diode_SOD-123,,1
Diode,D17,Diode_SOD-123,,1
10nF,C17,C_0402_1005Metric,,1
Soft-off switch,SW3,Panasonic_EVQPUL_EVQPUC,,1
Keyswitch,S19,CPG1316S01D02_front_mikefives,,1
Keyswitch,S22,CPG1316S01D02_front_mikefives,,1
Diode,D1,Diode_SOD-123,,1
Keyswitch,S17,CPG1316S01D02_front_mikefives,,1
1uF,C8,C_0402_1005Metric,,1
Diode,D32,Diode_SOD-123,,1
Keyswitch,S14,CPG1316S01D02_front_mikefives,,1
Keyswitch,S29,CPG1316S01D02_front_mikefives,,1
Diode,D27,Diode_SOD-123,,1
Diode,D13,Diode_SOD-123,,1
Diode,D9,Diode_SOD-123,,1
Diode,D8,Diode_SOD-123,,1
Keyswitch,S28,CPG1316S01D02_front_mikefives,,1
2.2uF,C20,C_0402_1005Metric,,1
1uF,C19,C_0402_1005Metric,,1
Conn_01x02,Batt1,JST_SHL_SM02B-SHLS-TF_1x02-1MP_P1.00mm_Horizontal,,1
Keyswitch,S6,CPG1316S01D02_front_mikefives,,1
Keyswitch,S10,CPG1316S01D02_front_mikefives,,1
Keyswitch,S33,CPG1316S01D02_front_mikefives,,1
Diode,D29,Diode_SOD-123,,1
Diode,D28,Diode_SOD-123,,1
Keyswitch,S3,CPG1316S01D02_front_mikefives,,1
Diode,D10,Diode_SOD-123,,1
Soft-off switch,SW6,Panasonic_EVQPUL_EVQPUC,,1
Diode,D26,Diode_SOD-123,,1
Keyswitch,S13,CPG1316S01D02_front_mikefives,,1
Keyswitch,S15,CPG1316S01D02_front_mikefives,,1
10nF,C5,C_0402_1005Metric,,1
Diode,D18,Diode_SOD-123,,1
Diode,D6,Diode_SOD-123,,1
Diode,D23,Diode_SOD-123,,1
Diode,D5,Diode_SOD-123,,1
Diode,D30,Diode_SOD-123,,1
Keyswitch,S9,CPG1316S01D02_front_mikefives,,1
Keyswitch,S35,CPG1316S01D02_front_mikefives,,1
Keyswitch,S12,CPG1316S01D02_front_mikefives,,1
Diode,D11,Diode_SOD-123,,1
Diode,D12,Diode_SOD-123,,1
Diode,D4,Diode_SOD-123,,1
Keyswitch,S8,CPG1316S01D02_front_mikefives,,1
Keyswitch,S34,CPG1316S01D02_front_mikefives,,1
Diode,D34,Diode_SOD-123,,1
10uF,C7,C_0603_1608Metric,,1
Conn_01x02,Batt2,JST_SHL_SM02B-SHLS-TF_1x02-1MP_P1.00mm_Horizontal,,1
Keyswitch,S7,CPG1316S01D02_front_mikefives,,1
2.2uH,L1,L_0805_2012Metric,,1
Keyswitch,S25,CPG1316S01D02_front_mikefives,,1
Keyswitch,S5,CPG1316S01D02_front_mikefives,,1
Keyswitch,S24,CPG1316S01D02_front_mikefives,,1
Keyswitch,S20,CPG1316S01D02_front_mikefives,,1
Diode,D14,Diode_SOD-123,,1
Reset,SW5,SW-SMD_L3.0-W2.0-LS3.5,,1
Diode,D36,Diode_SOD-123,,1
Keyswitch,S2,CPG1316S01D02_front_mikefives,,1
3.0V,VDD1,TestPoint_Pad_D1.0mm,,1

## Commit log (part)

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2025-11-09 Rename module and clean up dependencies
    Updated module name and removed unused dependency.
2025-11-09 initial commit of wafer keyboard configuration
2025-11-09 Add GitHub Actions workflow for build process
2025-11-09 Clean up build dependencies in module.yml
    Removed unnecessary build dependencies from module.yml
2025-11-09 Refactor board configuration for retention features
2025-11-09 Update Kconfig
2025-11-10 Add configuration for DCDC mode in Kconfig
2025-11-10 wafer.conf aktualisieren
2025-11-15 Add wafer layout configuration file json for Keymap Editor
2025-11-15 Refactor layout coordinates to include row/col
2025-11-19 Update GPIO configuration for kscan and col-gpios
2025-11-19 Change UART_TX pin from 8 to 9 in pinctrl
2025-11-19 Add USB logging snippet for wafer_left board
2025-11-19 Add USB SNIPPET UART configuration to wafer.dtsi
2025-11-19 Comment out unused GPIO configurations
    Comment out host-int-gpios and pmic-int-pin for clarity.
2025-11-20 moved to zephyr 4.1 (inital test)
2025-11-20 fixing initial
2025-11-20 reshuffle
2025-11-20 misspelled
2025-11-20 fixing
2025-11-20 resolving issues
2025-11-20 shuffle with kconfig
2025-11-20 add board.yml
2025-11-21 removed config
2025-11-21 removed cofigs
2025-11-21 added priority for the ext_power
2025-11-21 pmic tweak
2025-11-21 comment vin supply out
2025-11-21 display config
2025-11-21 added extra configs
2025-11-21 added zmk display
2025-11-21 fixing display
2025-11-21 fix0
2025-11-21 tests
2025-11-21 rewind changes
2025-11-21 removed display status (zmk_display still breaks the board)
2025-11-21 change lv memory size
2025-11-21 probably will work
2025-11-22 added memory
2025-11-22 adding extra configs
2025-11-22 configs for dedicated work queue and display
2025-11-22 changing the kconfig structure
2025-11-22 kconfig changes
2025-11-24 Added a new config menu
2025-11-25 Uncomment zmk-usb-logging snippet for boards
2025-11-25 Update wafer_left_defconfig
2025-11-25 Update wafer_right_defconfig
2025-11-25 Adding aditional memory and memory label
2025-11-25 adding voltage reporting fetch mode
2025-11-25 adding vin-supply to wafer.dtsi
2025-11-25 changed priority of the display
2025-11-25 EXT_power is now active high
2025-11-25 adding test keycodes
2025-11-27 Enable NPM1300 direct battery reporting mode
2025-11-27 Change battery reporting mode to NPM1300 direct
2025-11-29 removed regulator boot on
2025-11-29 Add default_transform configuration to wafer_right.dts
    Added default_transform with col-offset property.
2025-11-29 removing vin supply
2025-11-30 removed pull down
2025-11-30 added pcb files
2025-11-30 tweaked for toggling load switch
2025-11-30 tweaks to power management settings
2025-11-30 fixed
2025-12-01 fixing display on off
2025-12-01 editing
2025-12-01 added delay time
2025-12-02 minimal tweaks
2025-12-02 Corrected column offset for the right.dts
2025-12-02 changed keymap to default
2025-12-02 Initial release
2025-12-02 tap dance combo (fast double tap - bootloader, long press - turn off)
2025-12-15 Update README and add image assets
2025-12-15 renamed
2025-12-15 added extra photo
2026-04-10 Add case CNC files
2026-04-27 Add BOM section with links to production BOM and keyboard price CSV
    Added a section for the Bill of Materials (BOM) in the README.
2026-04-27 Fix Keyboard Price.csv: use comma delimiters and dot decimals
2026-04-27 Update CNC case price to $91 for the pair and recalculate totals
    Updated the keyboard price list and adjusted total values.
2026-04-27 Update CNC case to $91 per piece ($182 for the pair) and recalculate totals
    Updated prices and overall totals in the Keyboard Price CSV.
2026-04-27 Add README for Wafer ZMK BoardAdd README to boards/waferboard/wafer classifying board files by purpose
    This README provides an overview of the Wafer ZMK board, detailing the purpose of various files related to the build system, Kconfig options, devicetree descriptions, ZMK firmware configuration, and 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
2026-04-27 Add npm1300_vbat module skeleton (module.yml)
2026-04-27 Add Kconfig file for npm1300_vbat module
2026-04-27 Add CMakeLists.txt for npm1300_vbat module
2026-04-27 npm1300_vbat: add drivers/Kconfig wrapper
2026-04-27 npm1300_vbat: add ZMK_NPM1300_VBAT Kconfig symbol
2026-04-27 npm1300_vbat: add sensor CMakeLists.txt
2026-04-27 npm1300_vbat: add Zephyr sensor driver (VBAT via PMIC ADC)
2026-04-27 npm1300_vbat: add devicetree binding zmk,npm1300-vbat
2026-04-27 west.yml: switch to upstream zmkfirmware/zmk@main (was personal fork)
2026-04-27 wafer.dtsi: add npm1300_vbat_sensor node, repoint zmk,battery to it
2026-04-27 wafer.conf: enable battery reporting via npm1300_vbat sensor (lithium-voltage)
2026-04-27 README: document Battery/nPM1300 VBAT module + upstream zmk main build
2026-04-27 wafer_left_defconfig: replace stale FETCH_MODE_NPM1300_DIRECT with LITHIUM_VOLTAGE + npm1300_vbat module
2026-04-27 wafer_right_defconfig: replace stale FETCH_MODE_NPM1300_DIRECT with LITHIUM_VOLTAGE + npm1300_vbat module
2026-04-27 npm1300_vbat: use original fork I2C code (regs 0x05/0x00/0x11/0x15, FS 5000 mV, /1023)
2026-04-27 npm1300_vbat: fix YAML indentation in inner module.yml
2026-04-27 module.yml: add cmake/kconfig hooks so npm1300_vbat module is registered
2026-04-27 Add top-level CMakeLists.txt that pulls in modules/npm1300_vbat
2026-04-27 Add top-level Kconfig that sources modules/npm1300_vbat/Kconfig
2026-04-27 module.yml: point dts_root at modules/npm1300_vbat so binding YAML is found
2026-04-27 widgets/status.c: rename zmk_endpoints_selected() -> zmk_endpoint_get_selected() (upstream API rename)
2026-04-27 module.yml: revert dts_root to repo root (fixes layouts/ include)
2026-04-27 Move zmk,npm1300-vbat binding to top-level dts/bindings so it's discoverable
2026-04-28 Add MIT license scope for software code
2026-04-28 Add restricted hardware and design license
2026-04-28 Add split-license notice to README
2026-04-28 Replace root LICENSE with split-license notice
2026-04-28 Add split-license notice file
2026-04-28 Restore root LICENSE as recognizable MIT license
2026-06-21 Change revision from 'soft-off-plus' to 'main'
